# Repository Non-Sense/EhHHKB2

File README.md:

# EhHHKB2

[ブログ記事](https://blog.n0n5ense.com/blog/DcFo77JwRCHzNenNpN4wraU0PMD/)

Raspberry Pi Pico 2 W（RP2350 + CYW43）を載せた自作キーボード。
85 キー（8×11 マトリクス / 6 行）、USB HID と BLE HID の両対応で、
BLE は6ホストを記憶して切り替えられる。128x32 OLED で状態表示と設定操作ができる。

## ディレクトリ

| ディレクトリ | 内容 |
| --- | --- |
| `board/` | KiCad 10 のプロジェクト一式（回路図・PCB・プロジェクト専用ライブラリ） |
| `case/` | ケースの 3D データ（STEP）とレンダー画像 |
| `firmware/` | Pico SDK ベースのファームウェア（C）、ホスト単体テスト、ドキュメント生成スクリプト |

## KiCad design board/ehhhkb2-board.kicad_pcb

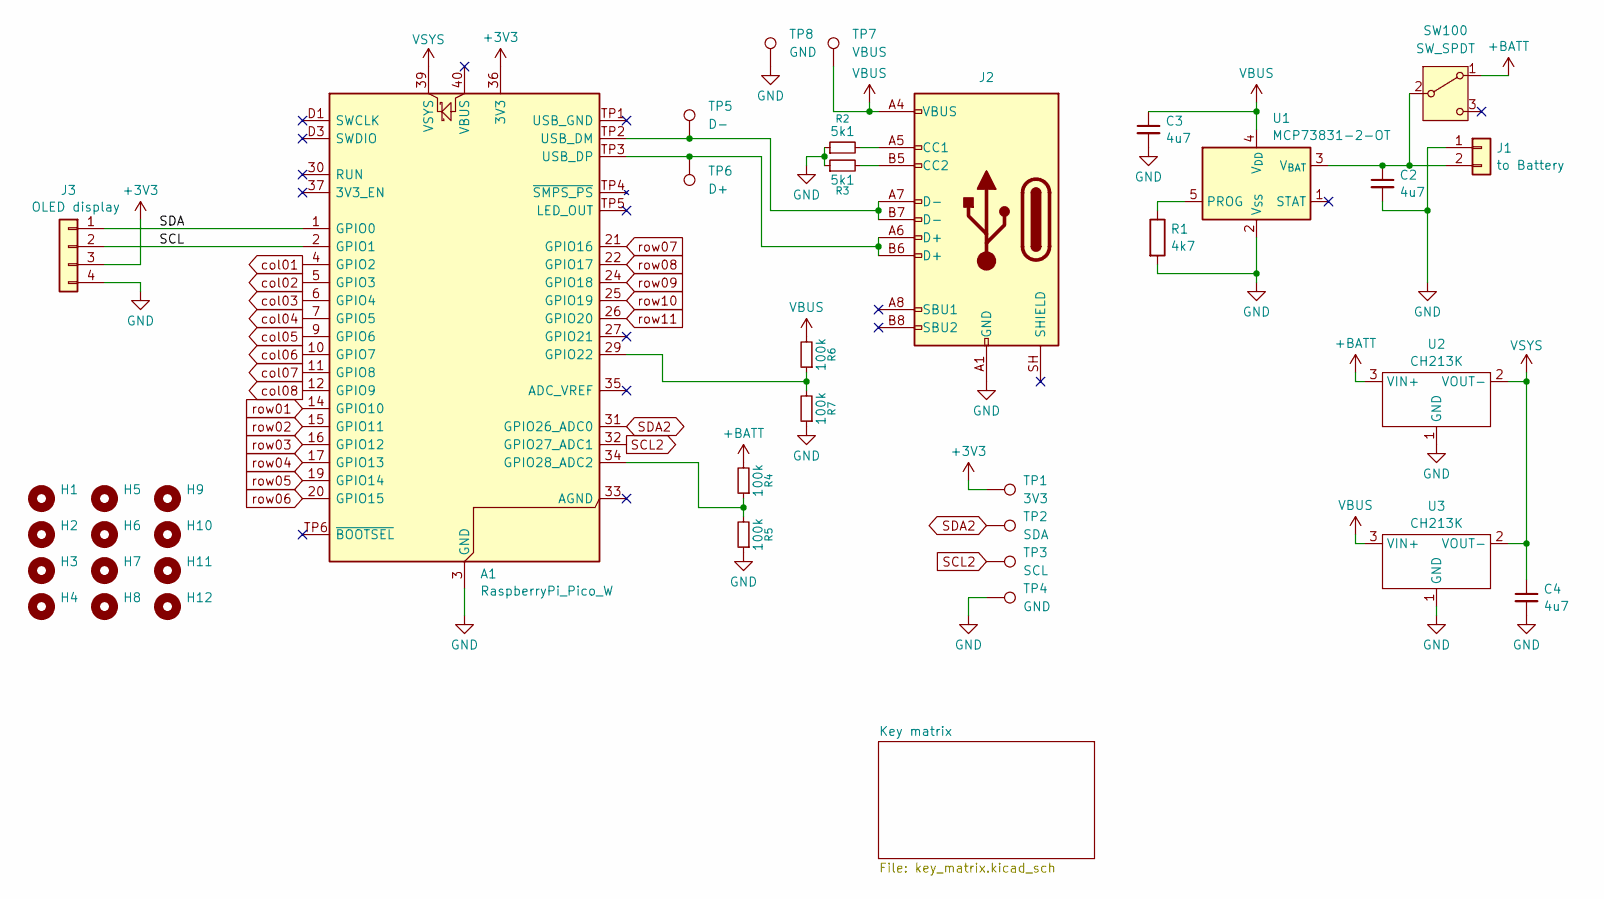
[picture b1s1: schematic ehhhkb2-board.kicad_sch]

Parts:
A1: RaspberryPi_Pico_W; RPi_Pico_SMD_Pins_No_SWD_No_Text
C2, C3, C4: 4u7; C_0603_1608Metric
H1, H2, H3, H4, H5, H6, H7, H8, H9, H10, H11, H12: MountingHole; MountingHole_2.2mm_M2
J1: to Battery; JST_PH_S2B-PH-K_1x02_P2.00mm_Horizontal
J2: USB_C_Receptacle_USB2.0_16P; 5077CR-16-SMC2
J3: OLED display; PinSocket_1x04_P2.54mm_Vertical
R1: 4k7; R_0603_1608Metric
R2, R3: 5k1; R_0603_1608Metric
R4, R5, R6, R7: 100k; R_0603_1608Metric
SW100: SW_SPDT; SW_Slide-03_Wuerth-WS-SLTV_10x2.5x6.4_P2.54mm
TP1: 3V3; TestPoint-0.75mm
TP2: SDA; TestPoint-0.75mm
TP3: SCL; TestPoint-0.75mm
TP4: GND; TestPoint-0.75mm
TP5: D-; TestPoint_Pad_D1.5mm
TP6: D+; TestPoint_Pad_D1.5mm
TP7: VBUS; TestPoint_Pad_D1.5mm
TP8: GND; TestPoint_Pad_D1.5mm
U1: MCP73831-2-OT; SOT-23-5
U2, U3: CH213K; SOT-23

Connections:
+3V3: A1.36 (3V3), J3.3, TP1.1 (1_1)
+BATT: R4.2, SW100.1 (A), U2.3 (VI+)
/SCL: A1.2 (GPIO1), J3.2
/SDA: A1.1 (GPIO0), J3.1
GND: A1.3 (GND), A1.8 (GND), A1.13 (GND), A1.18 (GND), A1.23 (GND), A1.28 (GND), A1.38 (GND), A1.D2 (GND), C2.2, C3.2, C4.2, J1.1, J2.A1 (GND), J2.A12 (GND), J2.B1 (GND), J2.B12 (GND), J3.4, R1.2, R2.1, R3.1, R5.1, R7.1, TP4.1 (1_1), TP8.1 (1_1), U1.2 (V_{SS}), U2.1 (GND), U3.1 (GND)
unnamed: A1.29 (GPIO22), R6.1, R7.2
unnamed: A1.34 (GPIO28_ADC2), R4.1, R5.2
unnamed: A1.TP2 (USB_DM), J2.A7 (D-), J2.B7 (D-), TP5.1 (1_1)
unnamed: A1.TP3 (USB_DP), J2.A6 (D+), J2.B6 (D+), TP6.1 (1_1)
unnamed: C2.1, J1.2, SW100.2 (B), U1.3 (V_{BAT})
unnamed: J2.A5 (CC1), R2.2
unnamed: J2.B5 (CC2), R3.2
unnamed: R1.1, U1.5 (PROG)
SCL2: A1.32 (GPIO27_ADC1), TP3.1 (1_1)
SDA2: A1.31 (GPIO26_ADC0), TP2.1 (1_1)
VBUS: C3.1, J2.A4 (VBUS), J2.A9 (VBUS), J2.B4 (VBUS), J2.B9 (VBUS), R6.2, TP7.1 (1_1), U1.4 (V_{DD}), U3.3 (VI+)
VSYS: A1.39 (VSYS), C4.1, U2.2 (VO-), U3.2 (VO-)
col01: A1.4 (GPIO2); also elsewhere on the board
col02: A1.5 (GPIO3); also elsewhere on the board
col03: A1.6 (GPIO4); also elsewhere on the board
col04: A1.7 (GPIO5); also elsewhere on the board
col05: A1.9 (GPIO6); also elsewhere on the board
col06: A1.10 (GPIO7); also elsewhere on the board
col07: A1.11 (GPIO8); also elsewhere on the board
col08: A1.12 (GPIO9); also elsewhere on the board
row01: A1.14 (GPIO10); also elsewhere on the board
row02: A1.15 (GPIO11); also elsewhere on the board
row03: A1.16 (GPIO12); also elsewhere on the board
row04: A1.17 (GPIO13); also elsewhere on the board
row05: A1.19 (GPIO14); also elsewhere on the board
row06: A1.20 (GPIO15); also elsewhere on the board
row07: A1.21 (GPIO16); also elsewhere on the board
row08: A1.22 (GPIO17); also elsewhere on the board
row09: A1.24 (GPIO18); also elsewhere on the board
row10: A1.25 (GPIO19); also elsewhere on the board
row11: A1.26 (GPIO20); also elsewhere on the board

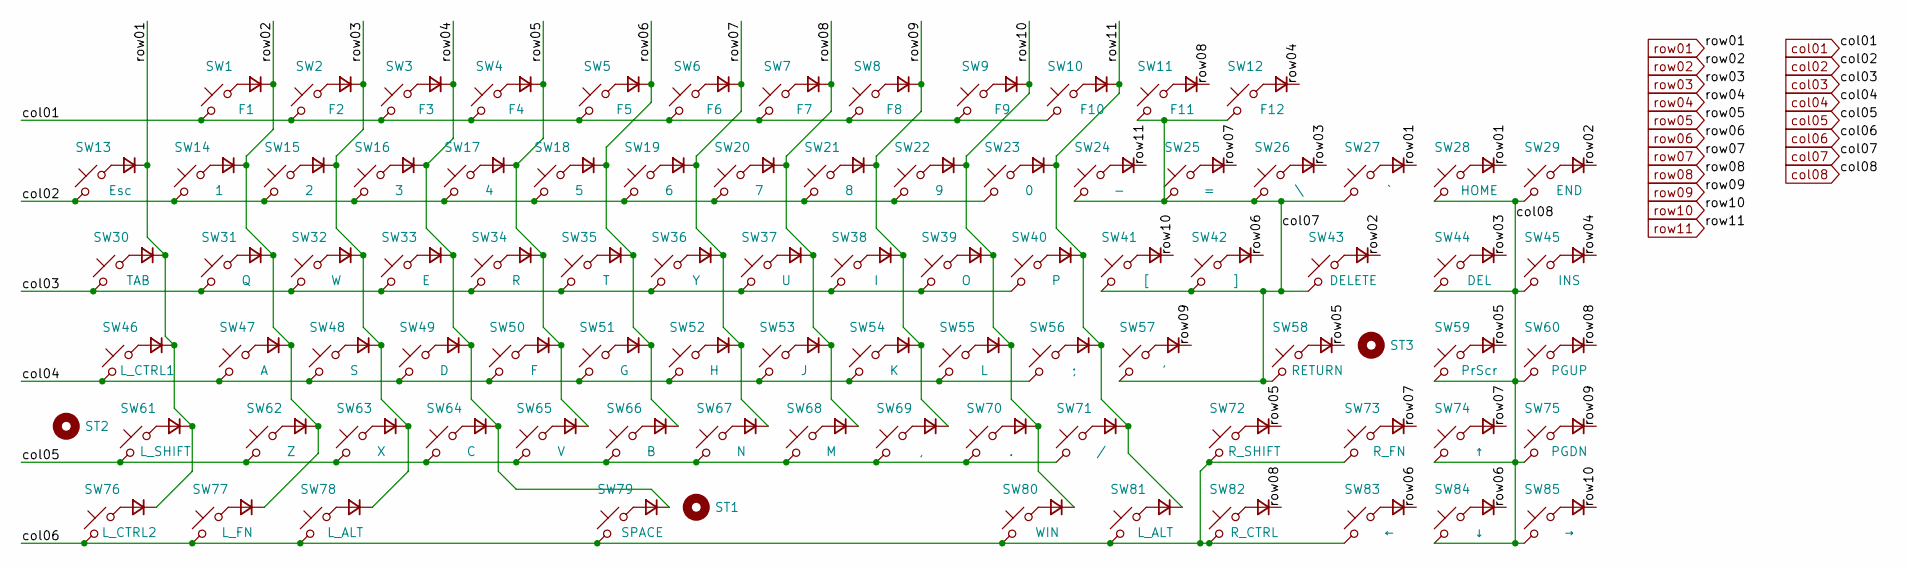
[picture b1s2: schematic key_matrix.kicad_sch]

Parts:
D1, D2, D3, D4, D5, D6, D7, D8, D9, D10, D11, D12, D13, D14, D15, D16, D17, D18, D19, D20, D21, D22, D23, D24, D25, D26, D27, D28, D29, D30, D31, D32, D33, D34, D35, D36, D37, D38, D39, D40, D41, D42, D43, D44, D45, D46, D47, D48, D49, D50, D51, D52, D53, D54, D55, D56, D57, D58, D59, D60, D61, D62, D63, D64, D65, D66, D67, D68, D69, D70, D71, D72, D73, D74, D75, D76, D77, D78, D79, D80, D81, D82, D83, D84, D85: D; D_SOD-123
ST1: Stabilizer_Cherry_MX_6.25u
ST2, ST3: Stabilizer_Cherry_MX_2.00u
SW1: F1; SW_Hotswap_Kailh_MX_1.00u
SW2: F2; SW_Hotswap_Kailh_MX_1.00u
SW3: F3; SW_Hotswap_Kailh_MX_1.00u
SW4: F4; SW_Hotswap_Kailh_MX_1.00u
SW5: F5; SW_Hotswap_Kailh_MX_1.00u
SW6: F6; SW_Hotswap_Kailh_MX_1.00u
SW7: F7; SW_Hotswap_Kailh_MX_1.00u
SW8: F8; SW_Hotswap_Kailh_MX_1.00u
SW9: F9; SW_Hotswap_Kailh_MX_1.00u
SW10: F10; SW_Hotswap_Kailh_MX_1.00u
SW11: F11; SW_Hotswap_Kailh_MX_1.00u
SW12: F12; SW_Hotswap_Kailh_MX_1.00u
SW13: Esc; SW_Hotswap_Kailh_MX_1.00u
SW14: 1; SW_Hotswap_Kailh_MX_1.00u
SW15: 2; SW_Hotswap_Kailh_MX_1.00u
SW16: 3; SW_Hotswap_Kailh_MX_1.00u
SW17: 4; SW_Hotswap_Kailh_MX_1.00u
SW18: 5; SW_Hotswap_Kailh_MX_1.00u
SW19: 6; SW_Hotswap_Kailh_MX_1.00u
SW20: 7; SW_Hotswap_Kailh_MX_1.00u
SW21: 8; SW_Hotswap_Kailh_MX_1.00u
SW22: 9; SW_Hotswap_Kailh_MX_1.00u
SW23: 0; SW_Hotswap_Kailh_MX_1.00u
SW24: -; SW_Hotswap_Kailh_MX_1.00u
SW25: =; SW_Hotswap_Kailh_MX_1.00u
SW26: \; SW_Hotswap_Kailh_MX_1.00u
SW27: `; SW_Hotswap_Kailh_MX_1.00u
SW28: HOME; SW_Hotswap_Kailh_MX_1.00u
SW29: END; SW_Hotswap_Kailh_MX_1.00u
SW30: TAB; SW_Hotswap_Kailh_MX_1.50u
SW31: Q; SW_Hotswap_Kailh_MX_1.00u
SW32: W; SW_Hotswap_Kailh_MX_1.00u
SW33: E; SW_Hotswap_Kailh_MX_1.00u
SW34: R; SW_Hotswap_Kailh_MX_1.00u
SW35: T; SW_Hotswap_Kailh_MX_1.00u
SW36: Y; SW_Hotswap_Kailh_MX_1.00u
SW37: U; SW_Hotswap_Kailh_MX_1.00u
SW38: I; SW_Hotswap_Kailh_MX_1.00u
SW39: O; SW_Hotswap_Kailh_MX_1.00u
SW40: P; SW_Hotswap_Kailh_MX_1.00u
SW41: [; SW_Hotswap_Kailh_MX_1.00u
SW42: ]; SW_Hotswap_Kailh_MX_1.00u
SW43: DELETE; SW_Hotswap_Kailh_MX_1.50u
SW44: DEL; SW_Hotswap_Kailh_MX_1.00u
SW45: INS; SW_Hotswap_Kailh_MX_1.00u
SW46: L_CTRL1; SW_Hotswap_Kailh_MX_1.75u
SW47: A; SW_Hotswap_Kailh_MX_1.00u
SW48: S; SW_Hotswap_Kailh_MX_1.00u
SW49: D; SW_Hotswap_Kailh_MX_1.00u
SW50: F; SW_Hotswap_Kailh_MX_1.00u
SW51: G; SW_Hotswap_Kailh_MX_1.00u
SW52: H; SW_Hotswap_Kailh_MX_1.00u
SW53: J; SW_Hotswap_Kailh_MX_1.00u
SW54: K; SW_Hotswap_Kailh_MX_1.00u
SW55: L; SW_Hotswap_Kailh_MX_1.00u
SW56: ;; SW_Hotswap_Kailh_MX_1.00u
SW57: '; SW_Hotswap_Kailh_MX_1.00u
SW58: RETURN; SW_Hotswap_Kailh_MX_2.25u
SW59: PrScr; SW_Hotswap_Kailh_MX_1.00u
SW60: PGUP; SW_Hotswap_Kailh_MX_1.00u
SW61: L_SHIFT; SW_Hotswap_Kailh_MX_2.25u
SW62: Z; SW_Hotswap_Kailh_MX_1.00u
SW63: X; SW_Hotswap_Kailh_MX_1.00u
SW64: C; SW_Hotswap_Kailh_MX_1.00u
SW65: V; SW_Hotswap_Kailh_MX_1.00u
SW66: B; SW_Hotswap_Kailh_MX_1.00u
SW67: N; SW_Hotswap_Kailh_MX_1.00u
SW68: M; SW_Hotswap_Kailh_MX_1.00u
SW69: ,; SW_Hotswap_Kailh_MX_1.00u
SW70: .; SW_Hotswap_Kailh_MX_1.00u
SW71: /; SW_Hotswap_Kailh_MX_1.00u
SW72: R_SHIFT; SW_Hotswap_Kailh_MX_1.75u
SW73: R_FN; SW_Hotswap_Kailh_MX_1.00u
SW74: ↑; SW_Hotswap_Kailh_MX_1.00u
SW75: PGDN; SW_Hotswap_Kailh_MX_1.00u
SW76: L_CTRL2; SW_Hotswap_Kailh_MX_1.25u
SW77: L_FN; SW_Hotswap_Kailh_MX_1.25u
SW78, SW81: L_ALT; SW_Hotswap_Kailh_MX_1.25u
SW79: SPACE; SW_Hotswap_Kailh_MX_6.25u
SW80: WIN; SW_Hotswap_Kailh_MX_1.25u
SW82: R_CTRL; SW_Hotswap_Kailh_MX_1.25u
SW83: ←; SW_Hotswap_Kailh_MX_1.00u
SW84: ↓; SW_Hotswap_Kailh_MX_1.00u
SW85: →; SW_Hotswap_Kailh_MX_1.00u

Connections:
unnamed: D1.2 (A), SW1.1
unnamed: D2.2 (A), SW2.1
unnamed: D3.2 (A), SW3.1
unnamed: D4.2 (A), SW4.1
unnamed: D5.2 (A), SW5.1
unnamed: D6.2 (A), SW6.1
unnamed: D7.2 (A), SW7.1
unnamed: D8.2 (A), SW8.1
unnamed: D9.2 (A), SW9.1
unnamed: D10.2 (A), SW10.1
unnamed: D11.2 (A), SW11.1
unnamed: D12.2 (A), SW12.1
unnamed: D13.2 (A), SW13.1
unnamed: D14.2 (A), SW14.1
unnamed: D15.2 (A), SW15.1
unnamed: D16.2 (A), SW16.1
unnamed: D17.2 (A), SW17.1
unnamed: D18.2 (A), SW18.1
unnamed: D19.2 (A), SW19.1
unnamed: D20.2 (A), SW20.1
unnamed: D21.2 (A), SW21.1
unnamed: D22.2 (A), SW22.1
unnamed: D23.2 (A), SW23.1
unnamed: D24.2 (A), SW24.1
unnamed: D25.2 (A), SW25.1
unnamed: D26.2 (A), SW26.1
unnamed: D27.2 (A), SW27.1
unnamed: D28.2 (A), SW28.1
unnamed: D29.2 (A), SW29.1
unnamed: D30.2 (A), SW30.1
unnamed: D31.2 (A), SW31.1
unnamed: D32.2 (A), SW32.1
unnamed: D33.2 (A), SW33.1
unnamed: D34.2 (A), SW34.1
unnamed: D35.2 (A), SW35.1
unnamed: D36.2 (A), SW36.1
unnamed: D37.2 (A), SW37.1
unnamed: D38.2 (A), SW38.1
unnamed: D39.2 (A), SW39.1
unnamed: D40.2 (A), SW40.1
unnamed: D41.2 (A), SW41.1
unnamed: D42.2 (A), SW42.1
unnamed: D43.2 (A), SW43.1
unnamed: D44.2 (A), SW44.1
unnamed: D45.2 (A), SW45.1
unnamed: D46.2 (A), SW46.1
unnamed: D47.2 (A), SW47.1
unnamed: D48.2 (A), SW48.1
unnamed: D49.2 (A), SW49.1
unnamed: D50.2 (A), SW50.1
unnamed: D51.2 (A), SW51.1
unnamed: D52.2 (A), SW52.1
unnamed: D53.2 (A), SW53.1
unnamed: D54.2 (A), SW54.1
unnamed: D55.2 (A), SW55.1
unnamed: D56.2 (A), SW56.1
unnamed: D57.2 (A), SW57.1
unnamed: D58.2 (A), SW58.1
unnamed: D59.2 (A), SW59.1
unnamed: D60.2 (A), SW60.1
unnamed: D61.2 (A), SW61.1
unnamed: D62.2 (A), SW62.1
unnamed: D63.2 (A), SW63.1
unnamed: D64.2 (A), SW64.1
unnamed: D65.2 (A), SW65.1
unnamed: D66.2 (A), SW66.1
unnamed: D67.2 (A), SW67.1
unnamed: D68.2 (A), SW68.1
unnamed: D69.2 (A), SW69.1
unnamed: D70.2 (A), SW70.1
unnamed: D71.2 (A), SW71.1
unnamed: D72.2 (A), SW72.1
unnamed: D73.2 (A), SW73.1
unnamed: D74.2 (A), SW74.1
unnamed: D75.2 (A), SW75.1
unnamed: D76.2 (A), SW76.1
unnamed: D77.2 (A), SW77.1
unnamed: D78.2 (A), SW78.1
unnamed: D79.2 (A), SW79.1
unnamed: D80.2 (A), SW80.1
unnamed: D81.2 (A), SW81.1
unnamed: D82.2 (A), SW82.1
unnamed: D83.2 (A), SW83.1
unnamed: D84.2 (A), SW84.1
unnamed: D85.2 (A), SW85.1
col01: SW1.2, SW2.2, SW3.2, SW4.2, SW5.2, SW6.2, SW7.2, SW8.2, SW9.2, SW10.2; also elsewhere on the board
col02: SW13.2, SW14.2, SW15.2, SW16.2, SW17.2, SW18.2, SW19.2, SW20.2, SW21.2, SW22.2, SW23.2; also elsewhere on the board
col03: SW30.2, SW31.2, SW32.2, SW33.2, SW34.2, SW35.2, SW36.2, SW37.2, SW38.2, SW39.2, SW40.2; also elsewhere on the board
col04: SW46.2, SW47.2, SW48.2, SW49.2, SW50.2, SW51.2, SW52.2, SW53.2, SW54.2, SW55.2, SW56.2; also elsewhere on the board
col05: SW61.2, SW62.2, SW63.2, SW64.2, SW65.2, SW66.2, SW67.2, SW68.2, SW69.2, SW70.2, SW71.2; also elsewhere on the board
col06: SW72.2, SW73.2, SW76.2, SW77.2, SW78.2, SW79.2, SW80.2, SW81.2, SW82.2, SW83.2; also elsewhere on the board
col07: SW11.2, SW12.2, SW24.2, SW25.2, SW26.2, SW27.2, SW41.2, SW42.2, SW43.2, SW57.2, SW58.2; also elsewhere on the board
col08: SW28.2, SW29.2, SW44.2, SW45.2, SW59.2, SW60.2, SW74.2, SW75.2, SW84.2, SW85.2; also elsewhere on the board
row01: D13.1 (K), D27.1 (K), D28.1 (K), D30.1 (K), D46.1 (K), D61.1 (K), D76.1 (K); also elsewhere on the board
row02: D1.1 (K), D14.1 (K), D29.1 (K), D31.1 (K), D43.1 (K), D47.1 (K), D62.1 (K), D77.1 (K); also elsewhere on the board
row03: D2.1 (K), D15.1 (K), D26.1 (K), D32.1 (K), D44.1 (K), D48.1 (K), D63.1 (K), D78.1 (K); also elsewhere on the board
row04: D3.1 (K), D12.1 (K), D16.1 (K), D33.1 (K), D45.1 (K), D49.1 (K), D64.1 (K), D79.1 (K); also elsewhere on the board
row05: D4.1 (K), D17.1 (K), D34.1 (K), D50.1 (K), D58.1 (K), D59.1 (K), D65.1 (K), D72.1 (K); also elsewhere on the board
row06: D5.1 (K), D18.1 (K), D35.1 (K), D42.1 (K), D51.1 (K), D66.1 (K), D83.1 (K), D84.1 (K); also elsewhere on the board
row07: D6.1 (K), D19.1 (K), D25.1 (K), D36.1 (K), D52.1 (K), D67.1 (K), D73.1 (K), D74.1 (K); also elsewhere on the board
row08: D7.1 (K), D11.1 (K), D20.1 (K), D37.1 (K), D53.1 (K), D60.1 (K), D68.1 (K), D82.1 (K); also elsewhere on the board
row09: D8.1 (K), D21.1 (K), D38.1 (K), D54.1 (K), D57.1 (K), D69.1 (K), D75.1 (K); also elsewhere on the board
row10: D9.1 (K), D22.1 (K), D39.1 (K), D41.1 (K), D55.1 (K), D70.1 (K), D80.1 (K), D85.1 (K); also elsewhere on the board
row11: D10.1 (K), D23.1 (K), D24.1 (K), D40.1 (K), D56.1 (K), D71.1 (K), D81.1 (K); also elsewhere on the board

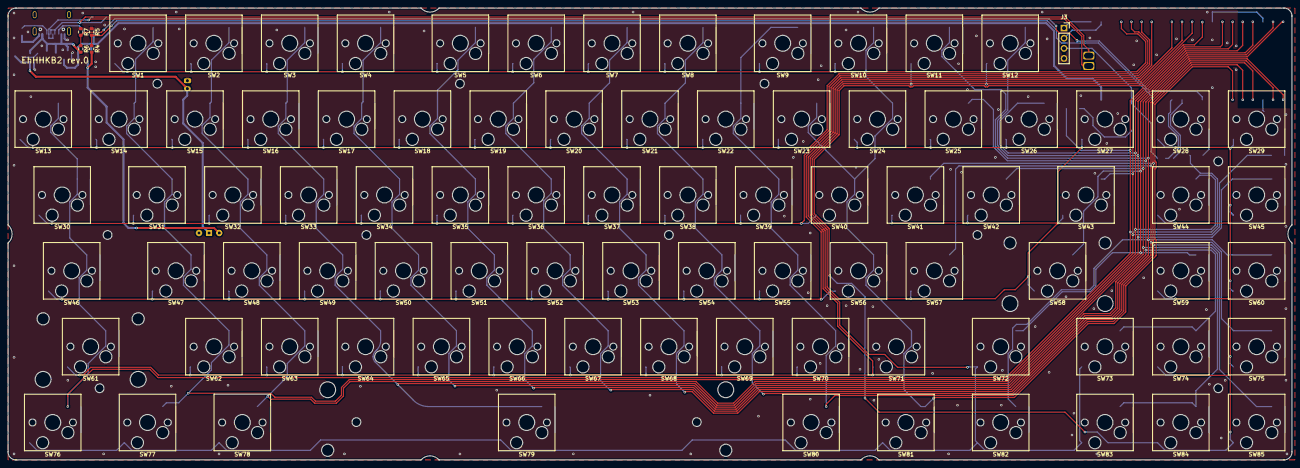
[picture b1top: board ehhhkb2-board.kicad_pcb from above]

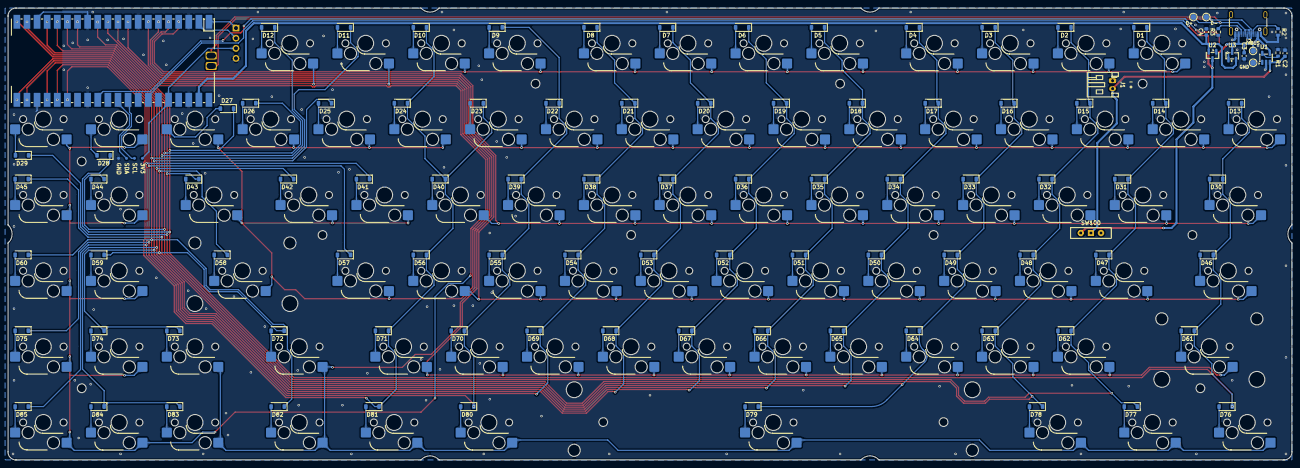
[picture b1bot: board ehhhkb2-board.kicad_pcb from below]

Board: 2 copper layers, 322.5 x 113.5 mm, 211 parts (106 on the bottom side), 121 nets.
